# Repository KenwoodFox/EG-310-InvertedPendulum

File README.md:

EG-310 Inverted Pendulum
========================

This project is full of blank media! It will need filling out and cleaning before production, you have been warned!

# Welcome!

Put a welcome here!

# Getting Started

## Cloning this repo

First, clone this repo (and optionally checkout a branch)

```shell
git clone https://github.com/KenwoodFox/InvertedPendulum.git
cd InvertedPendulum
```

## Init Submodules

Some libraries and resources are included as git submodules, run the following
command to initialize them before opening the main sch

(If you get a missing library error, make sure to do this!)

```shell
git submodule update --init --recursive
```

# Where is everything?!

Look to...
```shell
├── CAD                     # CAD and design files
├── Firmware                # Software and Firmware source code
├── Hardware                # PCB And component design files
└── Media
    ├── Notes               # Notes and scratch ideas/misc resources
    ├── Letters             # Status letters, letters of request, etc
    └── Presentations       # Presentations (CDR, FDR..)
```

# I just want to edit a single file!

Start by cloning this repo down and making a new branch, offical team communication
is through discord so hop on over any time! If you're new to git check out this video: https://youtu.be/mJ-qvsxPHpY

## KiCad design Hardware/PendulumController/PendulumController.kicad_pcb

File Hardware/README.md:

# Hardware

All the hardware for the inverted pendulum is made with (KiCAD)[https://www.kicad.org/]!

All the automation for this project is done with (KiBot)[https://github.com/INTI-CMNB/KiBot]

## Getting Started

Always clone this repo using submodules!

```shell
git clone --recurse-submodules https://github.com/KenwoodFox/EG-310-InvertedPendulum.git
```

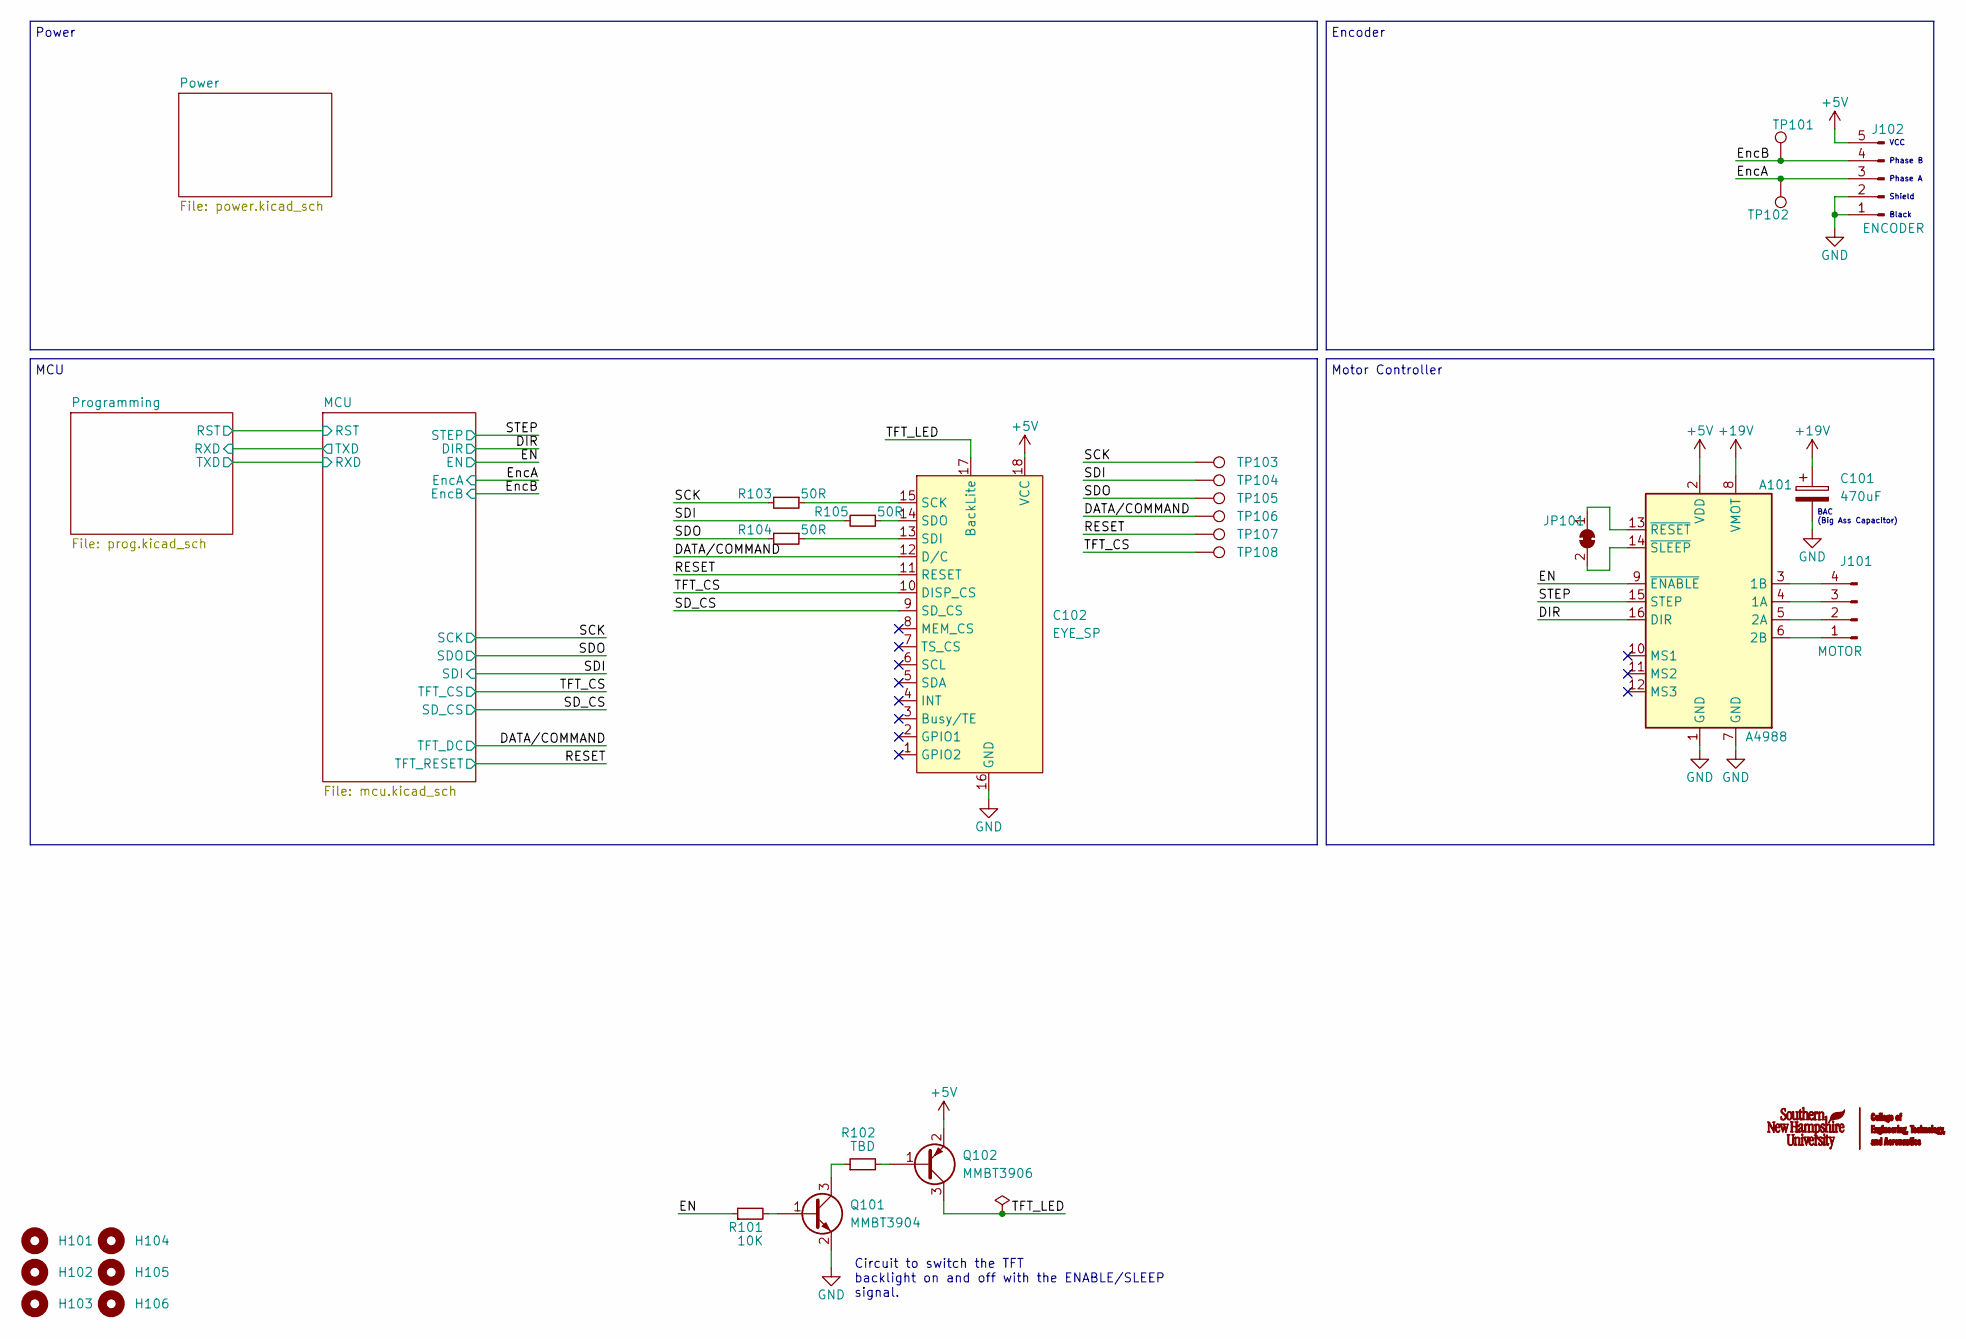
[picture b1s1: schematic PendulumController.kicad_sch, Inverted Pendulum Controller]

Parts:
A101: A4988; Pololu_Breakout-16_15.2x20.3mm
C101: 470uF; CP_Radial_D10.0mm_P3.80mm
C102: EYE_SP; Hirose_FH12-18S-0.5SH_1x18-1MP_P0.50mm_Horizontal
H101, H102, H103, H104, H105, H106: PiMountingHole; MountingHole_2.7mm
J101: MOTOR; JST_EH_B4B-EH-A_1x04_P2.50mm_Vertical
J102: ENCODER; JST_EH_B5B-EH-A_1x05_P2.50mm_Vertical
JP101: SolderJumper_2_Bridged; SolderJumper-2_P1.3mm_Bridged2Bar_Pad1.0x1.5mm
Q101: MMBT3904; SOT-23
Q102: MMBT3906; SOT-23
R101: 10K; R_0805_2012Metric
R102: TBD; R_0805_2012Metric
R103, R104, R105: 50R; R_0805_2012Metric
TP101, TP102: TestPoint; TestPoint_Pad_1.5x1.5mm
TP103, TP104, TP105, TP106, TP107, TP108: TestPoint; TestPoint_Pad_1.0x1.0mm

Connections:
+5V: A101.2 (VDD), C102.18 (VCC), J102.5, Q102.2 (E); also elsewhere on the board
+19V: A101.8 (VMOT), C101.1; also elsewhere on the board
/DATA/COMMAND: C102.12 (D/C), TP106.1; also elsewhere on the board
/DIR: A101.16 (DIR); also elsewhere on the board
/EN: A101.9 (~ENABLE), R101.1; also elsewhere on the board
/EncA: J102.3, TP102.1; also elsewhere on the board
/EncB: J102.4, TP101.1; also elsewhere on the board
/RESET: C102.11 (RESET), TP107.1; also elsewhere on the board
/SCK: R103.2, TP103.1; also elsewhere on the board
/SDI: R105.2, TP104.1; also elsewhere on the board
/SDO: R104.2, TP105.1; also elsewhere on the board
/SD_CS: C102.9 (SD_CS); also elsewhere on the board
/STEP: A101.15 (STEP); also elsewhere on the board
/TFT_CS: C102.10 (DISP_CS), TP108.1; also elsewhere on the board
/TFT_LED: C102.17 (BackLite), Q102.3 (C)
GND: A101.1 (GND), A101.7 (GND), C101.2, C102.16 (GND), J102.1, J102.2, Q101.2 (E); also elsewhere on the board
unnamed: A101.3 (1B), J101.4
unnamed: A101.4 (1A), J101.3
unnamed: A101.5 (2A), J101.2
unnamed: A101.6 (2B), J101.1
unnamed: A101.13 (~RESET), JP101.1 (A)
unnamed: A101.14 (~SLEEP), JP101.2 (B)
unnamed: C102.13 (SDI), R104.1
unnamed: C102.14 (SDO), R105.1
unnamed: C102.15 (SCK), R103.1
unnamed: Q101.1 (B), R101.2
unnamed: Q101.3 (C), R102.1
unnamed: Q102.1 (B), R102.2

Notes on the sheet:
Shield
Phase B
Power
Encoder
MCU
Circuit to switch the TFT backlight on and off with the ENABLE/SLEEP signal.
Black
BAC (Big Ass Capacitor)
Phase A
Motor Controller
VCC

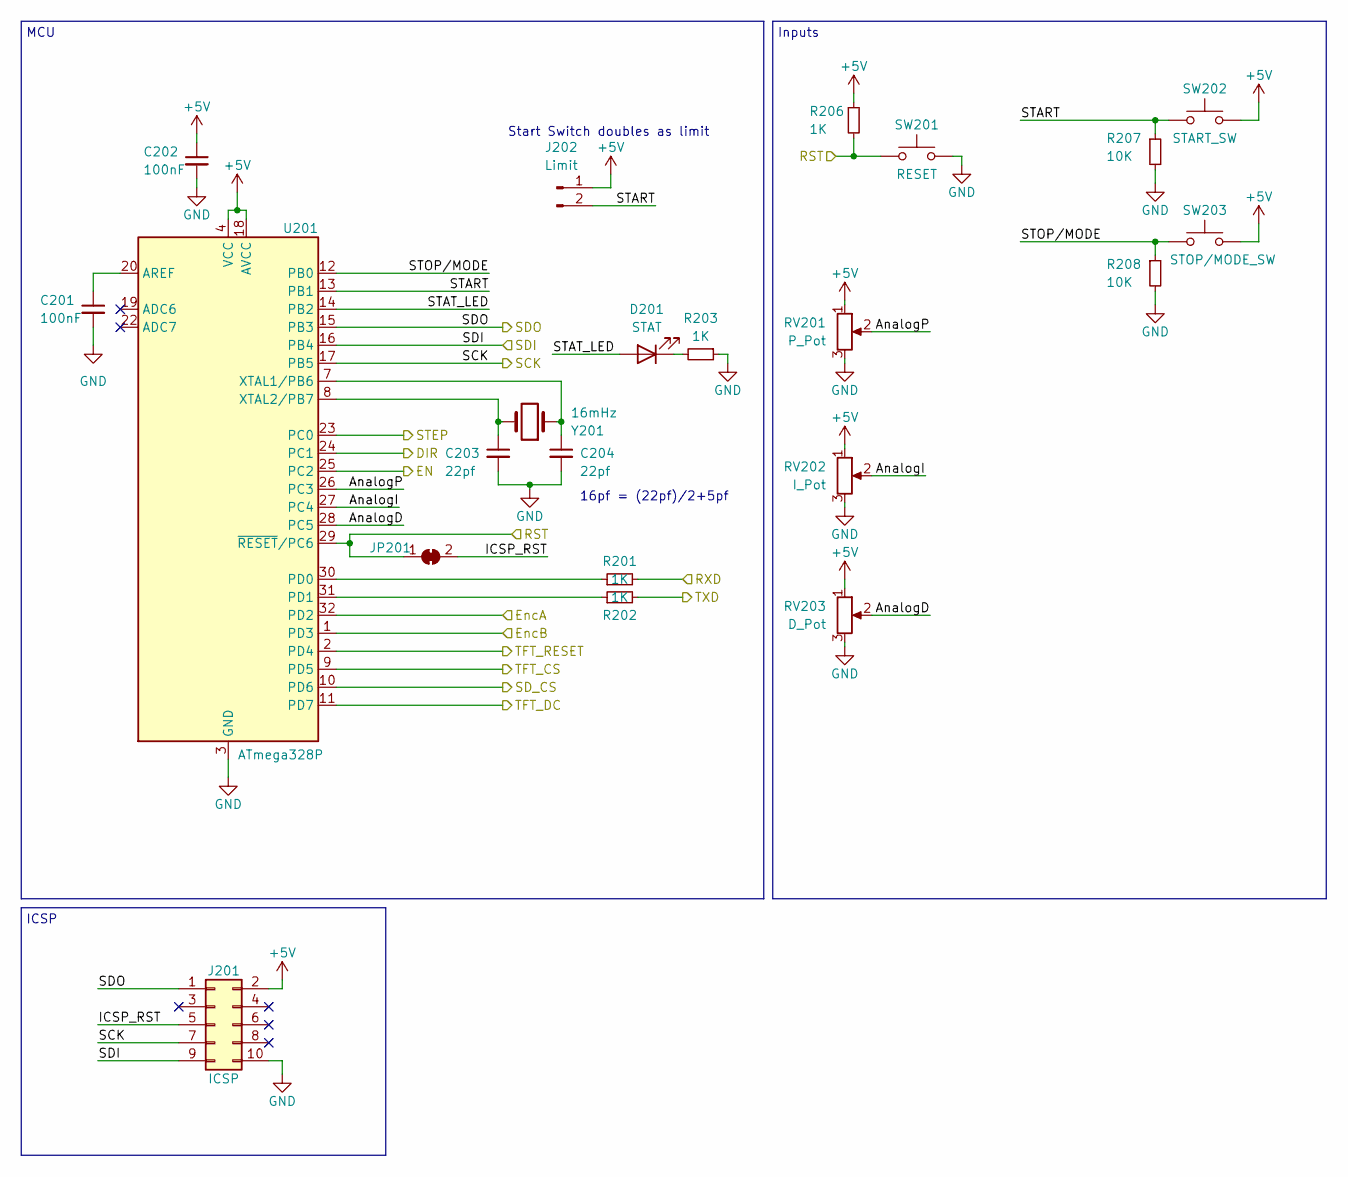
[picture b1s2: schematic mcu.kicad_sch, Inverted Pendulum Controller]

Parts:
C201, C202: 100nF; C_0805_2012Metric
C203, C204: 22pf; C_0805_2012Metric
D201: STAT; LED_0805_2012Metric
J201: ICSP; Tag-Connect_TC2050-IDC-FP_2x05_P1.27mm_Vertical
J202: Limit; JST_EH_B2B-EH-A_1x02_P2.50mm_Vertical
JP201: RSTBridge; SolderJumper-2_P1.3mm_Bridged_Pad1.0x1.5mm
R201, R202, R203, R206: 1K; R_0805_2012Metric
R207, R208: 10K; R_0805_2012Metric
RV201: P_Pot; JST_EH_B3B-EH-A_1x03_P2.50mm_Vertical
RV202: I_Pot; JST_EH_B3B-EH-A_1x03_P2.50mm_Vertical
RV203: D_Pot; JST_EH_B3B-EH-A_1x03_P2.50mm_Vertical
SW201: RESET; SW_PUSH_6mm_H5mm
SW202: START_SW; SW_PUSH_6mm_H5mm
SW203: STOP/MODE_SW; SW_PUSH_6mm_H5mm
U201: ATmega328P; TQFP-32_7x7mm_P0.8mm
Y201: 16mHz; Crystal_SMD_HC49-SD

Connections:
+5V: C202.1, J201.2, J202.1, R206.1, RV201.1, RV202.1, RV203.1, SW202.2, SW203.2, U201.4 (VCC), U201.6 (VCC), U201.18 (AVCC); also elsewhere on the board
/DATA/COMMAND: U201.11 (PD7); also elsewhere on the board
/DIR: U201.24 (PC1); also elsewhere on the board
/EN: U201.25 (PC2); also elsewhere on the board
/EncA: U201.32 (PD2); also elsewhere on the board
/EncB: U201.1 (PD3); also elsewhere on the board
/MCU/AnalogD: RV203.2, U201.28 (PC5)
/MCU/AnalogI: RV202.2, U201.27 (PC4)
/MCU/AnalogP: RV201.2, U201.26 (PC3)
/MCU/ICSP_RST: J201.5, JP201.2 (B)
/MCU/RST: JP201.1 (A), R206.2, SW201.1, U201.29 (~RESET/PC6); also elsewhere on the board
/MCU/RXD: R201.2; also elsewhere on the board
/MCU/START: J202.2, R207.1, SW202.1, U201.13 (PB1)
/MCU/STAT_LED: D201.2 (A), U201.14 (PB2)
/MCU/STOP/MODE: R208.1, SW203.1, U201.12 (PB0)
/MCU/TXD: R202.2; also elsewhere on the board
/RESET: U201.2 (PD4); also elsewhere on the board
/SCK: J201.7, U201.17 (PB5); also elsewhere on the board
/SDI: J201.9, U201.16 (PB4); also elsewhere on the board
/SDO: J201.1, U201.15 (PB3); also elsewhere on the board
/SD_CS: U201.10 (PD6); also elsewhere on the board
/STEP: U201.23 (PC0); also elsewhere on the board
/TFT_CS: U201.9 (PD5); also elsewhere on the board
GND: C201.2, C202.2, C203.2, C204.2, J201.10, R203.1, R207.2, R208.2, RV201.3, RV202.3, RV203.3, SW201.2, U201.3 (GND), U201.5 (GND), U201.21 (GND); also elsewhere on the board
unnamed: C201.1, U201.20 (AREF)
unnamed: C203.1, U201.8 (XTAL2/PB7), Y201.2
unnamed: C204.1, U201.7 (XTAL1/PB6), Y201.1
unnamed: D201.1 (K), R203.2
unnamed: R201.1, U201.30 (PD0)
unnamed: R202.1, U201.31 (PD1)

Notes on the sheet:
ICSP
Start Switch doubles as limit
MCU
Inputs
16pf = (22pf)/2+5pf

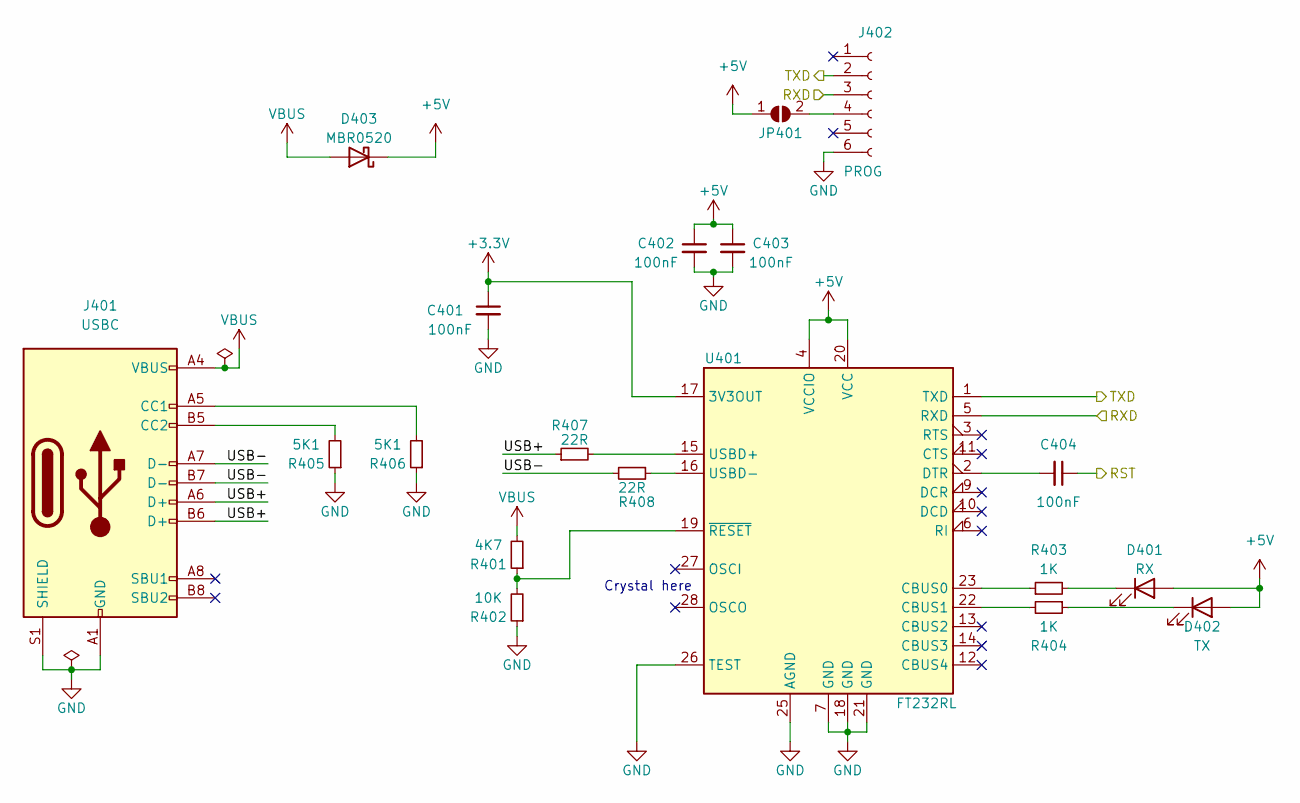
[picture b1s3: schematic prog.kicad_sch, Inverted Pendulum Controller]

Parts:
C401, C402, C403, C404: 100nF; C_0805_2012Metric
D401: RX; LED_0805_2012Metric
D402: TX; LED_0805_2012Metric
D403: MBR0520; D_SOD-123
J401: USBC; USB_C_Receptacle_XKB_U262-16XN-4BVC11
J402: PROG; PinSocket_1x06_P2.54mm_Vertical
JP401: SolderJumper_2_Open; SolderJumper-2_P1.3mm_Open_TrianglePad1.0x1.5mm
R401: 4K7; R_0805_2012Metric
R402: 10K; R_0805_2012Metric
R403, R404: 1K; R_0805_2012Metric
R405, R406: 5K1; R_0805_2012Metric
R407, R408: 22R; R_0805_2012Metric
U401: FT232RL; SSOP-28_5.3x10.2mm_P0.65mm

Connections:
+3.3V: C401.1, U401.17 (3V3OUT)
+5V: C402.1, C403.1, D401.2 (A), D402.2 (A), D403.1 (K), JP401.1 (A), U401.4 (VCCIO), U401.20 (VCC); also elsewhere on the board
/MCU/RST: C404.1; also elsewhere on the board
/MCU/RXD: J402.2, U401.1 (TXD); also elsewhere on the board
/MCU/TXD: J402.3, U401.5 (RXD); also elsewhere on the board
/Programming/USB+: J401.A6 (D+), J401.B6 (D+), R407.1
/Programming/USB-: J401.A7 (D-), J401.B7 (D-), R408.2
GND: C401.2, C402.2, C403.2, J401.A1 (GND), J401.A12 (GND), J401.B1 (GND), J401.B12 (GND), J401.S1 (SHIELD), J402.6, R402.1, R405.1, R406.1, U401.7 (GND), U401.18 (GND), U401.21 (GND), U401.25 (AGND), U401.26 (TEST); also elsewhere on the board
unnamed: C404.2, U401.2 (DTR)
unnamed: D401.1 (K), R403.2
unnamed: D402.1 (K), R404.1
unnamed: J401.A5 (CC1), R406.2
unnamed: J401.B5 (CC2), R405.2
unnamed: J402.4, JP401.2 (B)
unnamed: R401.1, R402.2, U401.19 (~RESET)
unnamed: R403.1, U401.23 (CBUS0)
unnamed: R404.2, U401.22 (CBUS1)
unnamed: R407.2, U401.15 (USBD+)
unnamed: R408.1, U401.16 (USBD-)
VBUS: D403.2 (A), J401.A4 (VBUS), J401.A9 (VBUS), J401.B4 (VBUS), J401.B9 (VBUS), R401.2

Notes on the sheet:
Crystal here

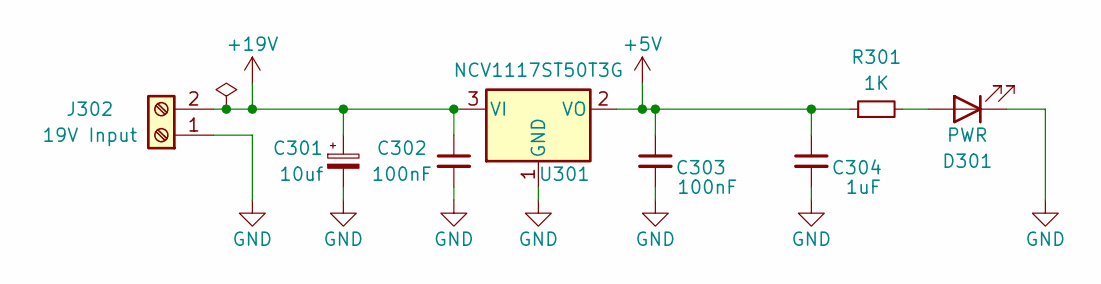
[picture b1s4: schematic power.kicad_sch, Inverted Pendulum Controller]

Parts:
C301: 10uf; CP_Elec_4x3
C302, C303: 100nF; C_0805_2012Metric
C304: 1uF; C_0805_2012Metric
D301: PWR; LED_0805_2012Metric
J302: 19V Input; TerminalBlock_Phoenix_MKDS-3-2-5.08_1x02_P5.08mm_Horizontal
R301: 1K; R_0805_2012Metric
U301: NCV1117ST50T3G; SOT-223

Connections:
+5V: C303.1, C304.1, R301.1, U301.2 (VO); also elsewhere on the board
+19V: C301.1, C302.1, J302.2, U301.3 (VI); also elsewhere on the board
GND: C301.2, C302.2, C303.2, C304.2, D301.1 (K), J302.1, U301.1 (GND); also elsewhere on the board
unnamed: D301.2 (A), R301.2

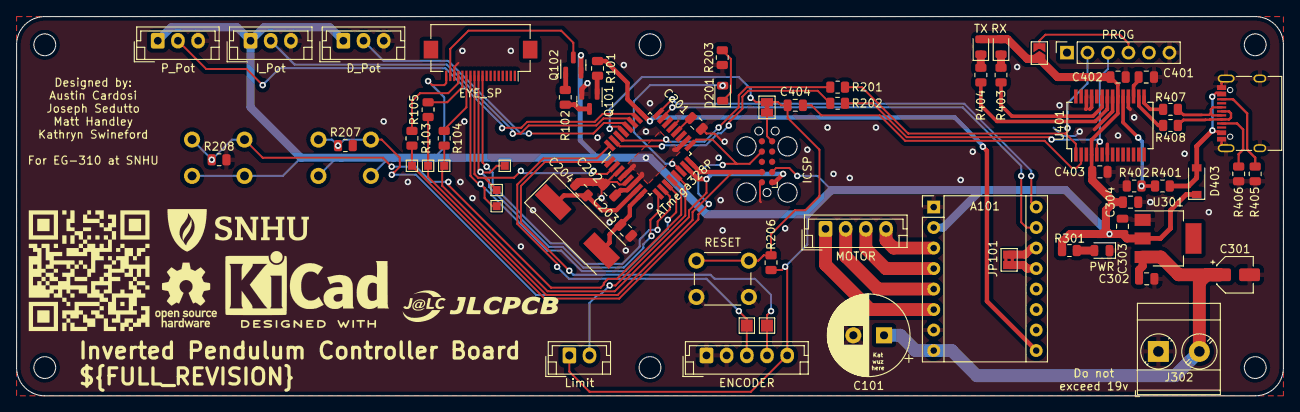
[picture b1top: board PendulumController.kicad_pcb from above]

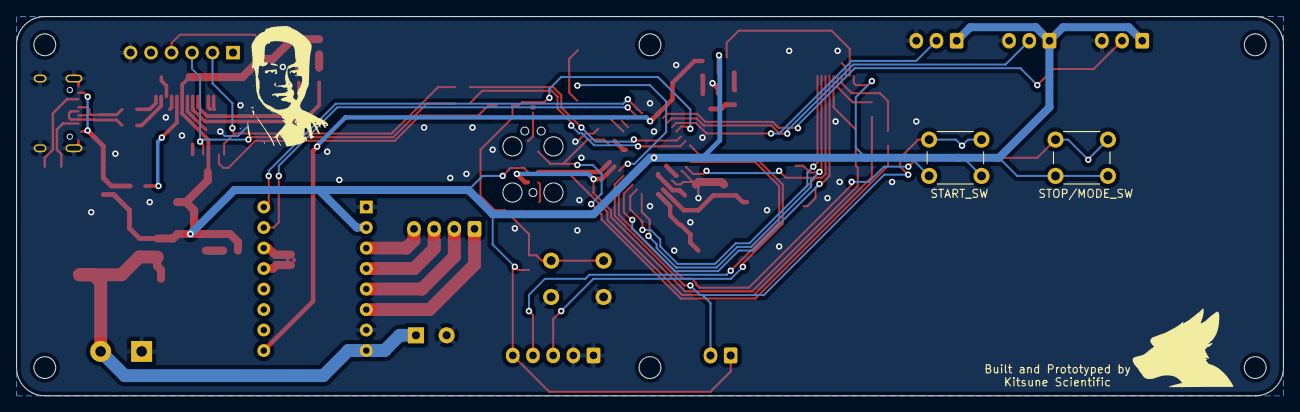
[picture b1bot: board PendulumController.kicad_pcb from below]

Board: 2 copper layers, 157.0 x 47.0 mm, 78 parts (2 on the bottom side), 60 nets.

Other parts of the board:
QRCODE: LOGO; custom_silkscreen
SNHU_NEW***: LOGO; SNHU_NEW

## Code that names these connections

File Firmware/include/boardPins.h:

#include <Arduino.h>

#ifndef _BOARD_PINS_H
#define _BOARD_PINS_H

// LEDs
#define STAT_LED 10 // PB2

// Power Control
#define ENABLE A2 // PC2

// Motor
// #define STEP A0 // PC0
// #define DIR A1  // PC1
#define STEP 7  // PC0
#define DIR 8   // PC1
#define ENC_A 2 // PD2
#define ENC_B 3 // PD3

// Buttons and Inputs
#define PPIN A3     // PC3
#define IPIN A4     // Also SDA, PC4
#define DPIN A5     // Also SCL, PC5
#define STOP_MODE 8 // PB0
#define START 9     // PB1

// TFT Display
#define TFT_RST 4 // PD4
#define TFT_CS 5  // PD5
#define SD_CS 6   // PD6
#define TFT_DC 9  // PD7

#endif

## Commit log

2023-01-03 Inital commit
2023-01-03 Boilerplate project
2023-01-03 Add kenwoodfox libs
2023-01-03 Cleanup board layout, cleanup firmware and go to bed, this is a sturdy place to start a new project!
2023-01-03 Configure kibot config
2023-01-03 Add power flags
2023-01-03 Add MPU library to firmware
2023-01-03 Spitballin' with Matt
2023-01-03 Cleanup readme and fix ERC
2023-01-03 Pull new changes from custom libs
2023-01-03 Add notes for timer code
2023-01-03 Add TFT connector
2023-01-04 Add sample presentation in LaTeX
2023-01-04 Improve readme and clean notes
2023-01-04 Add stencil cutouts and bump kicad libs
2023-01-04 Boilerplate ConOps
2023-01-04 Hi Joe :D
    I changed the README
2023-01-05 Pad ConOps
2023-01-05 Clean up board design with embedded power supply
2023-01-05 Finalize input location
2023-01-05 Add temporary logo files
2023-01-05 Compile logo into ConOps
2023-01-05 Fix DRC check
2023-01-05 Check backlight power circuit before printing
2023-01-05 Add comments, clean formatting and proper aspect ratio for Matt
2023-01-05 Fix typo in logo
2023-01-05 no need to keep building firmware unless we actually modify it
2023-01-05 Configure all pins
2023-01-05 Use new encoder library
2023-01-06 CopOps Draft #1
    The team worked together to draft a complete con ops :D
2023-01-06 Add note for windows users
2023-01-06 Fix formatting on .tex
2023-01-06 Ignore all dvi
2023-01-09 Add cosmetic badge
2023-01-09 Rebase with conops
2023-01-09 Bump!
2023-01-09 fixup! Bump!
2023-01-09 Cache, typos and remove bloat
2023-01-09 Last bump, confirm cache and set schematic width
2023-01-09 Use SVG graphics
2023-01-09 Try this
2023-01-09 Rehash before building
2023-01-09 Do not cache
2023-01-09 Fixup conversion path
2023-01-09 ConOps Draft (#2)
    Submitting as soon as folder is available
2023-01-09 Setup project libre and meeting notes
2023-01-09 Docs and Cosmetic (#4)
    Great!
2023-01-10 temp firmware
2023-01-10 @matt fix build of new pres
2023-01-10 Fix the presentation :D
    I forgot the reasources file D:
2023-01-10 Update Pendulum Team Hours Worked.xlsx
    Updated Worked Hours to Represent Class Time
2023-01-11 USB C!
2023-01-11 Circuiting
2023-01-11 Add extra tidbits and sketches to conops
2023-01-11 Hours Worked Update
    Updated the Hours Worked to Account for Today's Class
2023-01-12 Try to merge hours into projectLibre (#6)
2023-01-12 Merge ProjectLibre
    Merging this, future branches will reference main.
2023-01-13 Add new pod file to brightspace
2023-01-15 Adafruit lib
2023-01-16 Issues with adafruit spi default speed
2023-01-16 Create weekly report template
2023-01-16 Create weekly report for 9-16
2023-01-16 Clean up weekly status report for meeting today
2023-01-16 Meeting Minutes and Status Report Week 2
    Kat and I did the Meeting Minutes and the Status Report :D
2023-01-16 Remove junk
2023-01-16 Bump .gitignore
2023-01-16 Convert docx to markdown
2023-01-16 Submit to brigthspace
2023-01-18 Messily convert slideshow conops to skeleton conops (beamer to article)
2023-01-18 Created the PDP article crap :O
2023-01-18 Update PDP.tex
    Added further subsections
2023-01-18 Updated Hours Worked
    Updated Hours Worked to Take Into Account Today's Class
2023-01-21 Update Pendulum Team Hours Worked.xlsx
    Added the time it took to do the status report
2023-01-21 1/18 Meeting Minute + Weekly Status Report
    Added the weekly status report to the branch :)
2023-01-22 Quickly convert meeting minutes to markdown
2023-01-22 Cleanup first two sections
2023-01-22 Revamp conops
2023-01-22 Add likelyhood
2023-01-22 Clean up pdp article form
2023-01-22 Include all the bare essentials including autocitations
2023-01-22 Pause work on pdp article here
2023-01-23 Add PDP Draft and Updated Hours Worked
2023-01-23 Create Meeting Minutes 1-22.docx
    Updated the meeting minutes folder to include today's meeting :)
2023-01-23 Convert docx to markdown again
2023-01-23 ConOps Post review (#7)
2023-01-23 Napkin math lol, found it
2023-01-23 Create BOM
2023-01-23 Bump BOM
2023-01-23 Add elements for PDP draft
2023-01-23 PDP Draft #1, Meeting Minutes, Hours Worked
    We finished PDP Draft #1 today.
    I updated the meeting minutes and hours worked to reflect this.
2023-01-28 Added this week's status report
    Updated the hours worked document and added this weeks status report!
2023-01-29 Feat/pdp draft #1 (#8)
    Hey this is great! PDP draft went well, I'm merging this in favor of a new branch.
2023-01-29 Boilerplate PDP
2023-01-29 End of meeting
2023-01-30 Small layout improvements
2023-01-30 Add external research
2023-01-30 Add functional requirements
2023-01-30 More boilerplate and import
2023-01-30 Add risk assessment
2023-01-30 Clean
2023-01-30 Physical requirements
2023-01-30 Add all tables
2023-01-30 Add design concepts
2023-01-30 Last pictures!
2023-01-30 Do more
2023-01-30 Add conops
2023-01-30 Add last three slides
2023-01-30 Bump weekly report
2023-01-30 Add picture to system description
2023-01-30 Add last
2023-01-30 Add circuit board
2023-01-30 Change theme
2023-01-30 Add all remaining
2023-02-01 Add notes!
2023-02-01 fixup! Add notes!
2023-02-01 Final version!
2023-02-01 PDP Revision 2 (#9)
    Good job today!
2023-02-06 Testing
    Testing List
2023-02-06 Clean repo
2023-02-06 Super basic modeling
    My files from today's meeting
2023-02-09 Add upstream EYESPI
2023-02-09 Add new connector
2023-02-12 Route all
2023-02-12 Fix ERC
2023-02-12 Add limit siwtch
2023-02-12 Bump meeting minutes
2023-02-13 Add usb terminators
2023-02-14 Bump cache
2023-02-15 Silkscreen!
2023-02-15 NOW its perfect
2023-02-15 Design verified! Last checkmark complete
2023-02-15 Make sure CDR stays in the tree
2023-02-15 Add slightly better docs
2023-02-15 Fix service
2023-02-15 Bump checkout
2023-02-16 Docs (#14)
2023-02-16 Last cleanups!
2023-02-16 Add ordering instructions
2023-02-16 V1 Board (#3)
2023-02-16 fixup! V1 Board (#3)
2023-02-16 Add weekly releases to team report
2023-02-19 Boilerplate new CDR
2023-02-19 Boilerplate all blank CDR slides
2023-02-19 Consoldate resources
2023-02-19 Add up to requirments
2023-02-19 Add up to ordering status
2023-02-19 Add schematic
2023-02-19 Include system design
2023-02-19 Import matt's closeups
    Co-Authored By: @Matthew-Handley
2023-02-19 Add FreeCAD closeups
2023-02-19 Create verification slides
2023-02-20 Bump exploded view
    Co-Authored By: @Matthew-Handley
2023-02-20 Finish up meeting
    Co-Authored By: @Matthew-Handley
2023-02-20 Added My CAD Filed to CDR Branch
    These files are still in Inventor format, I will export them to .steps at a later time.
2023-02-20 Do not include "OldVersions"
2023-02-20 Rework CAD directory
2023-02-20 Reorganization of My CAD Directory
    Reorganized and Renamed My CAD Upload
2023-02-20 Add RTD to readme
2023-02-20 Fix gold leftover on docs
2023-02-20 Add safety and material trade study 1
2023-02-20 Fill remaining slides
2023-02-20 Add last few pages
2023-02-20 Bump begin
2023-02-20 AJMK
2023-02-20 Add discoruse slide
2023-02-20 Add extra overview slide and notes
2023-02-20 Review from technical writer
    Spellcheck
    Move slides around, should have electrcial/software as well as mechanical sections
    Clean up safety slides
    Add PID slide
2023-02-21 Implement technical writer reformat
2023-02-22 Populate notes
2023-02-22 Pretty solid
2023-02-22 assign everyone
2023-02-22 CDR Prep (#11)
    This is good to go thank you @AustinC63
2023-02-24 Inital assembly
2023-02-24 Add all inital cad pieces
2023-02-24 Add inital Frame model
2023-02-24 Move components
2023-02-24 Bump bezel
2023-02-24 Bump CAD again for matt
2023-02-24 Bump frame and first electrical components
2023-02-24 Add assembly
2023-02-24 Bump CAD a little for Matt
2023-02-24 Rename components
2023-02-26 Better fit for screen
2023-02-26 Bump bezel again
2023-02-26 Bump push button
2023-02-27 Bump
2023-02-27 Bump push button (again)
2023-02-28 Loading bar
2023-02-28 Tidy BOM
2023-02-28 Im calling this a new animation
2023-02-28 Tidy inital software
2023-02-28 Dont delay in setup
2023-02-28 Working bitmap drawings!
2023-02-28 Build with encoder
2023-02-28 Fast video
2023-02-28 Tidy brd
2023-02-28 more work
2023-02-28 Add full qr code support
2023-02-28 Add access holes:
2023-03-02 Create stencil
2023-03-04 Weird debugging issue
2023-03-06 Configure for usbasp
2023-03-12 include vbus bypass diode
2023-03-12 Add photos
2023-03-12 Clean code
2023-03-12 More cleaning
2023-03-18 Clean cad
2023-03-18 Revision 2 board
2023-03-19 Add missing components to assy drawing
2023-03-20 confirming motor
2023-03-20 boilerplate user inputs
2023-03-20 Scootch trace
2023-03-20 stuff
2023-03-25 Bump model with panels
2023-03-25 Add plans for endplates and sides
2023-03-29 Bump frame
2023-03-30 Bump test code
2023-04-01 Add inital stuff for encoder holder
2023-04-02 Send new models to all printers
2023-04-08 bump cad
2023-04-09 Boilerplate calibrate.h
2023-04-10 Almost
2023-04-10 Almost almost
2023-04-10 Inital Frame and motor assembly (#13)
2023-04-10 Create Pendulum PID Test Readiness Review.pptx
    :D
2023-04-10 Firmware (#15)
    Merged for PRR
2023-04-10 TRR Presentation (#17)
    Approved, merging for trr presentation
2023-04-16 Create new motor adapter
2023-04-16 Add spinup
2023-04-16 Primitive I term
2023-04-17 Update Pendulum Project Verification Matrix.xlsx
    Updated Again :D
2023-04-19 Add READMEs
2023-04-19 Include tft function for demo
2023-04-19 Adding the Final Presentation
2023-04-19 Final tune
2023-04-19 Add final reports as binaries
2023-04-19 Fix a bug where sources were not updated
2023-04-19 Final Report :D
    YAAAAAAY!!!
2023-04-19 Final Presentation (#18)
